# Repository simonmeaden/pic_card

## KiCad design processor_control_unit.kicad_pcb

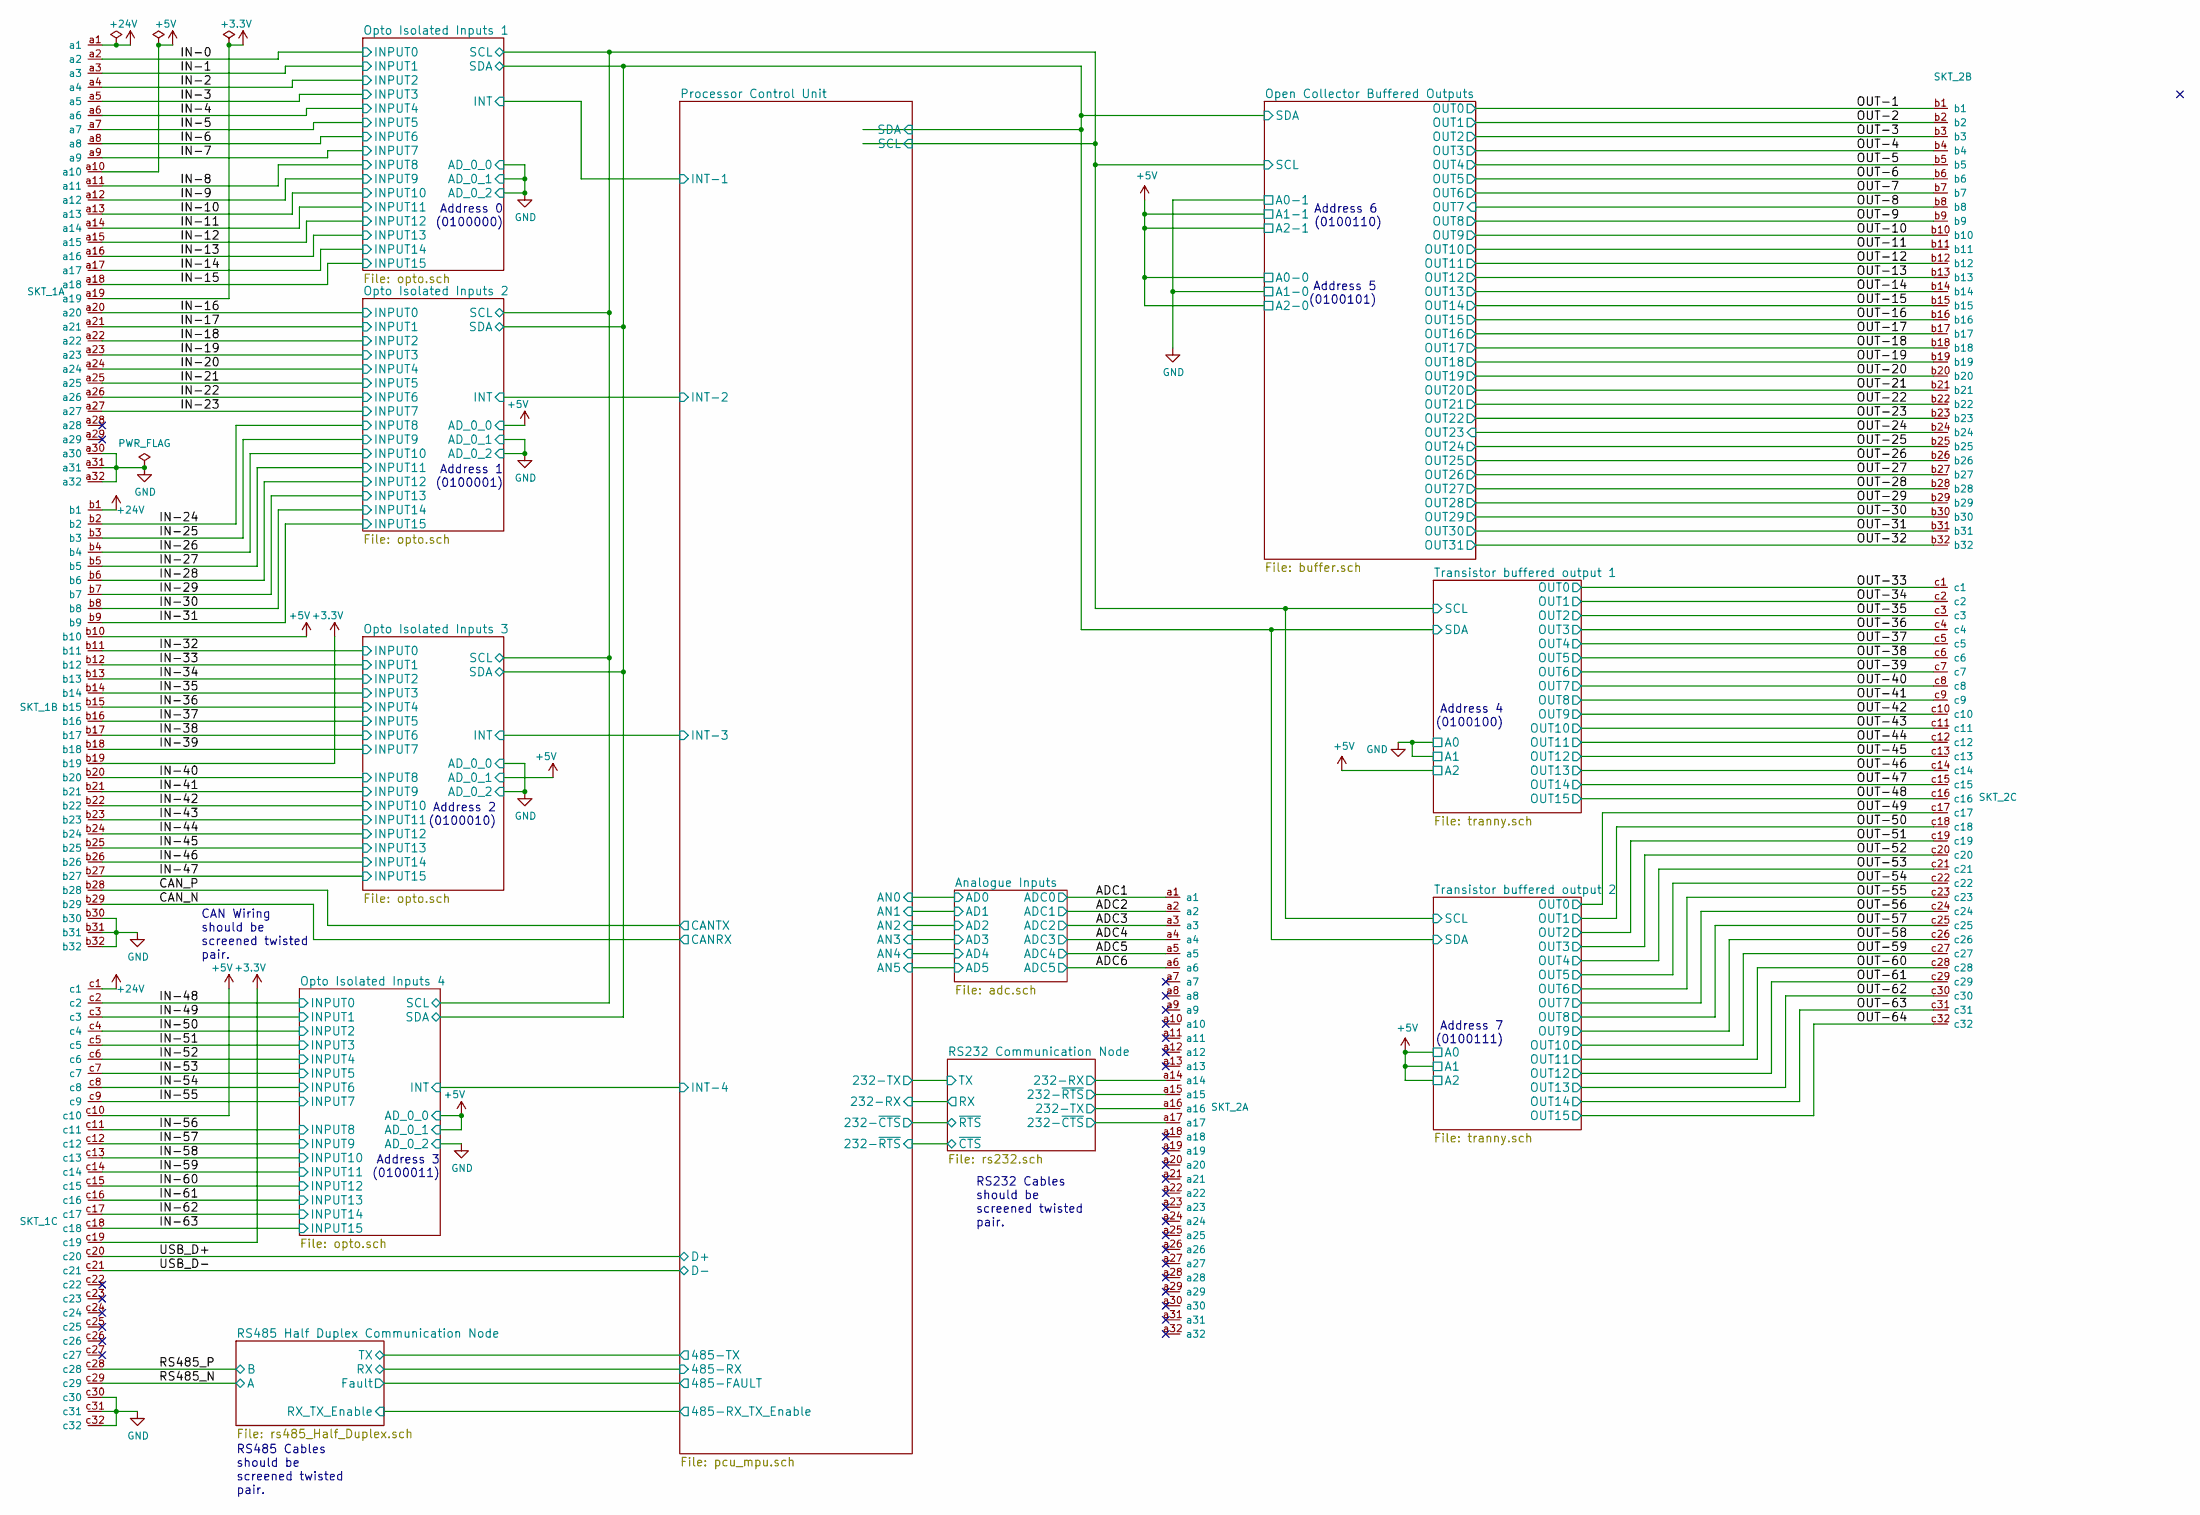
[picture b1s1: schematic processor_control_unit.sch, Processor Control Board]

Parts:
SKT_1, SKT_2: Conn_03x32_MountingPin_Pancon_RightAngled_Male; Pancon_100_3x32_P2.54mm_RightAngled_Male_PCB

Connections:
+3V3: SKT_1.a19, SKT_1.b19, SKT_1.c19
+5V: SKT_1.a10, SKT_1.b10, SKT_1.c10; also elsewhere on the board
+24V: SKT_1.a1, SKT_1.b1, SKT_1.c1; also elsewhere on the board
/ADC1: SKT_2.a1; also elsewhere on the board
/ADC2: SKT_2.a2; also elsewhere on the board
/ADC3: SKT_2.a3; also elsewhere on the board
/ADC4: SKT_2.a4; also elsewhere on the board
/ADC5: SKT_2.a5; also elsewhere on the board
/ADC6: SKT_2.a6; also elsewhere on the board
/CAN_N: SKT_1.b29; also elsewhere on the board
/CAN_P: SKT_1.b28; also elsewhere on the board
/IN-0: SKT_1.a2; also elsewhere on the board
/IN-1: SKT_1.a3; also elsewhere on the board
/IN-2: SKT_1.a4; also elsewhere on the board
/IN-3: SKT_1.a5; also elsewhere on the board
/IN-4: SKT_1.a6; also elsewhere on the board
/IN-5: SKT_1.a7; also elsewhere on the board
/IN-6: SKT_1.a8; also elsewhere on the board
/IN-7: SKT_1.a9; also elsewhere on the board
/IN-8: SKT_1.a11; also elsewhere on the board
/IN-9: SKT_1.a12; also elsewhere on the board
/IN-10: SKT_1.a13; also elsewhere on the board
/IN-11: SKT_1.a14; also elsewhere on the board
/IN-12: SKT_1.a15; also elsewhere on the board
/IN-13: SKT_1.a16; also elsewhere on the board
/IN-14: SKT_1.a17; also elsewhere on the board
/IN-15: SKT_1.a18; also elsewhere on the board
/IN-16: SKT_1.a20; also elsewhere on the board
/IN-17: SKT_1.a21; also elsewhere on the board
/IN-18: SKT_1.a22; also elsewhere on the board
/IN-19: SKT_1.a23; also elsewhere on the board
/IN-20: SKT_1.a24; also elsewhere on the board
/IN-21: SKT_1.a25; also elsewhere on the board
/IN-22: SKT_1.a26; also elsewhere on the board
/IN-23: SKT_1.a27; also elsewhere on the board
/IN-24: SKT_1.b2; also elsewhere on the board
/IN-25: SKT_1.b3; also elsewhere on the board
/IN-26: SKT_1.b4; also elsewhere on the board
/IN-27: SKT_1.b5; also elsewhere on the board
/IN-28: SKT_1.b6; also elsewhere on the board
/IN-29: SKT_1.b7; also elsewhere on the board
/IN-30: SKT_1.b8; also elsewhere on the board
/IN-31: SKT_1.b9; also elsewhere on the board
/IN-32: SKT_1.b11; also elsewhere on the board
/IN-33: SKT_1.b12; also elsewhere on the board
/IN-34: SKT_1.b13; also elsewhere on the board
/IN-35: SKT_1.b14; also elsewhere on the board
/IN-36: SKT_1.b15; also elsewhere on the board
/IN-37: SKT_1.b16; also elsewhere on the board
/IN-38: SKT_1.b17; also elsewhere on the board
/IN-39: SKT_1.b18; also elsewhere on the board
/IN-40: SKT_1.b20; also elsewhere on the board
/IN-41: SKT_1.b21; also elsewhere on the board
/IN-42: SKT_1.b22; also elsewhere on the board
/IN-43: SKT_1.b23; also elsewhere on the board
/IN-44: SKT_1.b24; also elsewhere on the board
/IN-45: SKT_1.b25; also elsewhere on the board
/IN-46: SKT_1.b26; also elsewhere on the board
/IN-47: SKT_1.b27; also elsewhere on the board
/IN-48: SKT_1.c2; also elsewhere on the board
/IN-49: SKT_1.c3; also elsewhere on the board
/IN-50: SKT_1.c4; also elsewhere on the board
/IN-51: SKT_1.c5; also elsewhere on the board
/IN-52: SKT_1.c6; also elsewhere on the board
/IN-53: SKT_1.c7; also elsewhere on the board
/IN-54: SKT_1.c8; also elsewhere on the board
/IN-55: SKT_1.c9; also elsewhere on the board
/IN-56: SKT_1.c11; also elsewhere on the board
/IN-57: SKT_1.c12; also elsewhere on the board
/IN-58: SKT_1.c13; also elsewhere on the board
/IN-59: SKT_1.c14; also elsewhere on the board
/IN-60: SKT_1.c15; also elsewhere on the board
/IN-61: SKT_1.c16; also elsewhere on the board
/IN-62: SKT_1.c17; also elsewhere on the board
/IN-63: SKT_1.c18; also elsewhere on the board
/OUT-1: SKT_2.b1; also elsewhere on the board
/OUT-2: SKT_2.b2; also elsewhere on the board
/OUT-3: SKT_2.b3; also elsewhere on the board
/OUT-4: SKT_2.b4; also elsewhere on the board
/OUT-5: SKT_2.b5; also elsewhere on the board
/OUT-6: SKT_2.b6; also elsewhere on the board
/OUT-7: SKT_2.b7; also elsewhere on the board
/OUT-8: SKT_2.b8; also elsewhere on the board
/OUT-9: SKT_2.b9; also elsewhere on the board
/OUT-10: SKT_2.b10; also elsewhere on the board
/OUT-11: SKT_2.b11; also elsewhere on the board
/OUT-12: SKT_2.b12; also elsewhere on the board
/OUT-13: SKT_2.b13; also elsewhere on the board
/OUT-14: SKT_2.b14; also elsewhere on the board
/OUT-15: SKT_2.b15; also elsewhere on the board
/OUT-16: SKT_2.b16; also elsewhere on the board
/OUT-17: SKT_2.b17; also elsewhere on the board
/OUT-18: SKT_2.b18; also elsewhere on the board
/OUT-19: SKT_2.b19; also elsewhere on the board
/OUT-20: SKT_2.b20; also elsewhere on the board
/OUT-21: SKT_2.b21; also elsewhere on the board
/OUT-22: SKT_2.b22; also elsewhere on the board
/OUT-23: SKT_2.b23; also elsewhere on the board
/OUT-24: SKT_2.b24; also elsewhere on the board
/OUT-25: SKT_2.b25; also elsewhere on the board
/OUT-26: SKT_2.b26; also elsewhere on the board
/OUT-27: SKT_2.b27; also elsewhere on the board
/OUT-28: SKT_2.b28; also elsewhere on the board
/OUT-29: SKT_2.b29; also elsewhere on the board
/OUT-30: SKT_2.b30; also elsewhere on the board
/OUT-31: SKT_2.b31; also elsewhere on the board
/OUT-32: SKT_2.b32; also elsewhere on the board
/OUT-33: SKT_2.c1; also elsewhere on the board
/OUT-34: SKT_2.c2; also elsewhere on the board
/OUT-35: SKT_2.c3; also elsewhere on the board
/OUT-36: SKT_2.c4; also elsewhere on the board
/OUT-37: SKT_2.c5; also elsewhere on the board
/OUT-38: SKT_2.c6; also elsewhere on the board
/OUT-39: SKT_2.c7; also elsewhere on the board
/OUT-40: SKT_2.c8; also elsewhere on the board
/OUT-41: SKT_2.c9; also elsewhere on the board
/OUT-42: SKT_2.c10; also elsewhere on the board
/OUT-43: SKT_2.c11; also elsewhere on the board
/OUT-44: SKT_2.c12; also elsewhere on the board
/OUT-45: SKT_2.c13; also elsewhere on the board
/OUT-46: SKT_2.c14; also elsewhere on the board
/OUT-47: SKT_2.c15; also elsewhere on the board
/OUT-48: SKT_2.c16; also elsewhere on the board
/OUT-49: SKT_2.c17; also elsewhere on the board
/OUT-50: SKT_2.c18; also elsewhere on the board
/OUT-51: SKT_2.c19; also elsewhere on the board
/OUT-52: SKT_2.c20; also elsewhere on the board
/OUT-53: SKT_2.c21; also elsewhere on the board
/OUT-54: SKT_2.c22; also elsewhere on the board
/OUT-55: SKT_2.c23; also elsewhere on the board
/OUT-56: SKT_2.c24; also elsewhere on the board
/OUT-57: SKT_2.c25; also elsewhere on the board
/OUT-58: SKT_2.c26; also elsewhere on the board
/OUT-59: SKT_2.c27; also elsewhere on the board
/OUT-60: SKT_2.c28; also elsewhere on the board
/OUT-61: SKT_2.c29; also elsewhere on the board
/OUT-62: SKT_2.c30; also elsewhere on the board
/OUT-63: SKT_2.c31; also elsewhere on the board
/OUT-64: SKT_2.c32; also elsewhere on the board
/RS232 Communication Node/232-RX: SKT_2.a14; also elsewhere on the board
/RS232 Communication Node/232-TX: SKT_2.a16; also elsewhere on the board
/RS232 Communication Node/232-~CTS~: SKT_2.a17; also elsewhere on the board
/RS232 Communication Node/232-~RTS~: SKT_2.a15; also elsewhere on the board
/RS485_N: SKT_1.c29; also elsewhere on the board
/RS485_P: SKT_1.c28; also elsewhere on the board
/USB_D+: SKT_1.c20; also elsewhere on the board
/USB_D-: SKT_1.c21; also elsewhere on the board
GND: SKT_1.a30, SKT_1.a31, SKT_1.a32, SKT_1.b30, SKT_1.b31, SKT_1.b32, SKT_1.c30, SKT_1.c31, SKT_1.c32; also elsewhere on the board

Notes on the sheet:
CAN Wiring should be screened twisted pair.
Address 0 (0100000)
Address 5 (0100101)
Address 4 (0100100)
Address 2 (0100010)
Address 3 (0100011)
Address 1 (0100001)
Address 6 (0100110)
Address 7 (0100111)
RS232 Cables should be screened twisted pair.
RS485 Cables should be screened twisted pair.

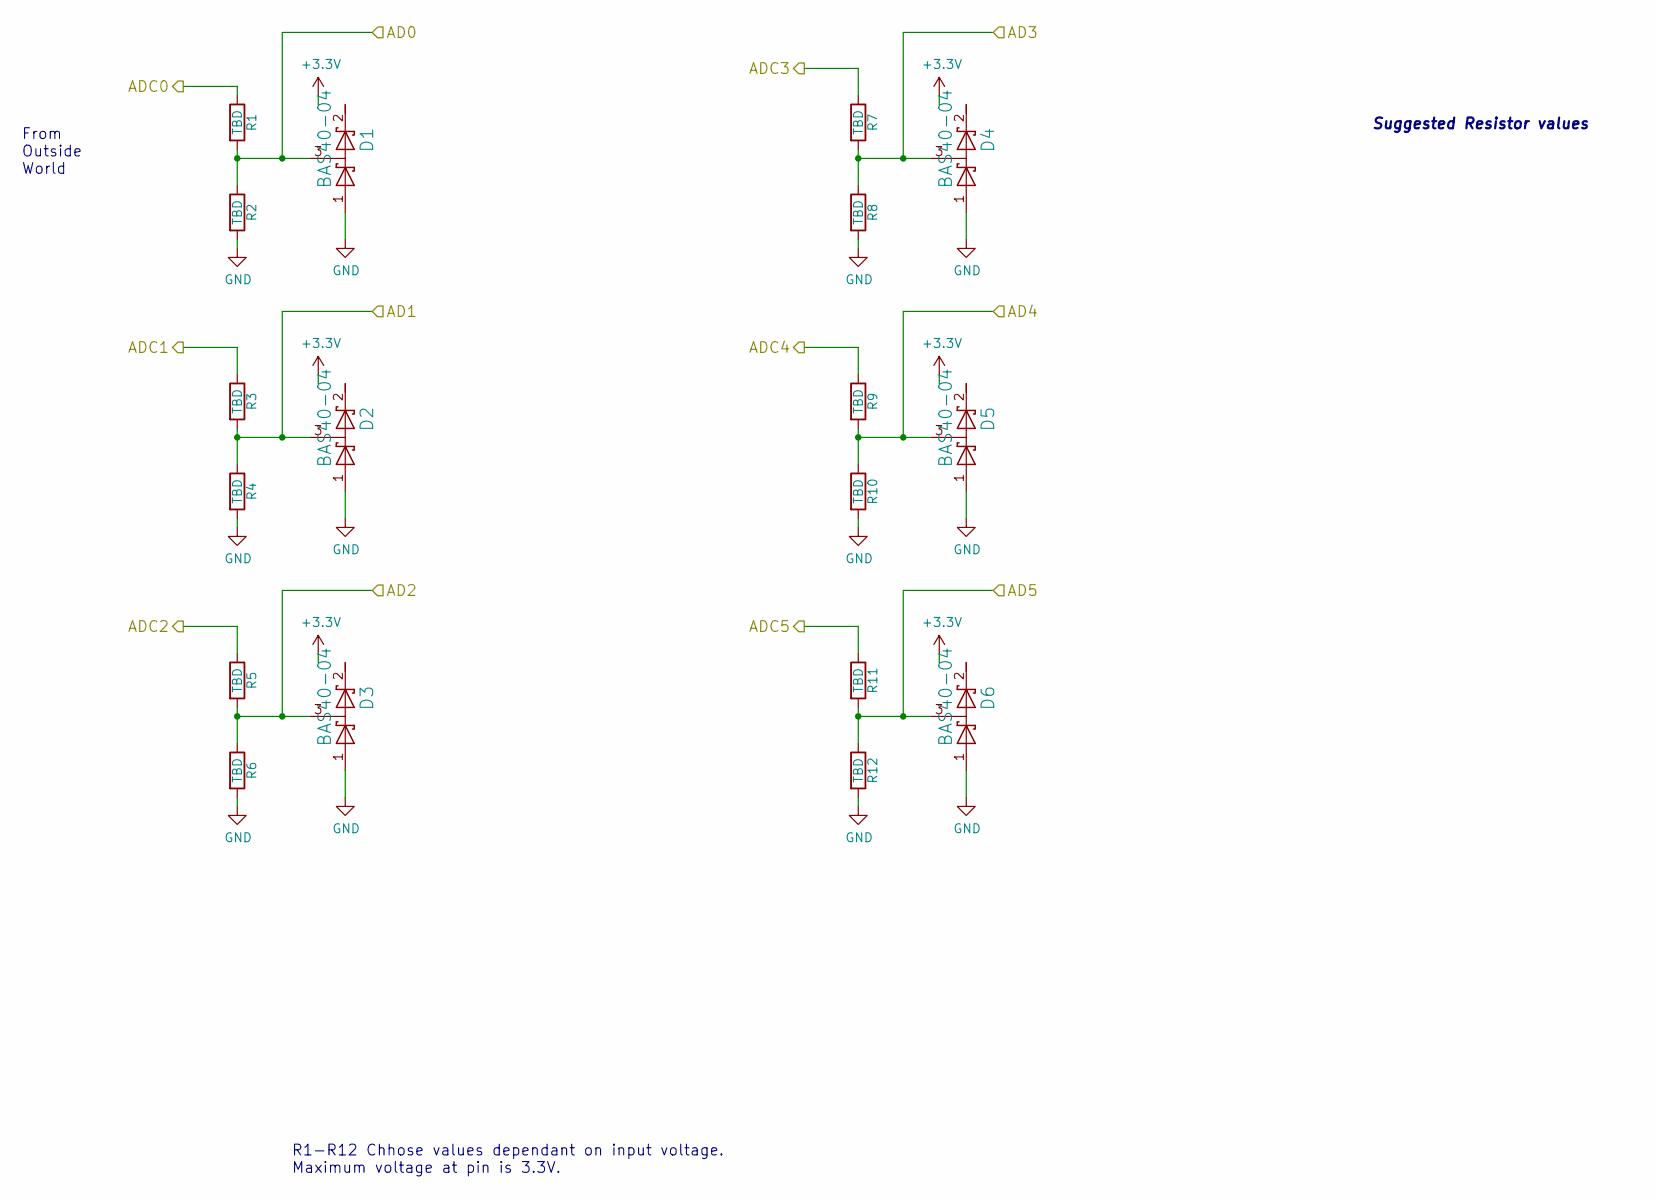
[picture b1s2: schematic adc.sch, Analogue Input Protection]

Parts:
D1, D2, D3, D4, D5, D6: BAS40-04; SOT23
R1, R2, R3, R4, R5, R6, R7, R8, R9, R10, R11, R12: TBD; R_0805_2012Metric

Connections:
/ADC1: R1.1; also elsewhere on the board
/ADC2: R3.1; also elsewhere on the board
/ADC3: R5.1; also elsewhere on the board
/ADC4: R7.1; also elsewhere on the board
/ADC5: R9.1; also elsewhere on the board
/ADC6: R11.1; also elsewhere on the board
/Analogue Inputs/AD0: D1.3 (common), R1.2, R2.1; also elsewhere on the board
/Analogue Inputs/AD1: D2.3 (common), R3.2, R4.1; also elsewhere on the board
/Analogue Inputs/AD2: D3.3 (common), R5.2, R6.1; also elsewhere on the board
/Analogue Inputs/AD3: D4.3 (common), R7.2, R8.1; also elsewhere on the board
/Analogue Inputs/AD4: D5.3 (common), R9.2, R10.1; also elsewhere on the board
/Analogue Inputs/AD5: D6.3 (common), R11.2, R12.1; also elsewhere on the board
GND: D1.1 (A), D2.1 (A), D3.1 (A), D4.1 (A), D5.1 (A), D6.1 (A), R2.2, R4.2, R6.2, R8.2, R10.2, R12.2; also elsewhere on the board

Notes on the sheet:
From Outside World
R1-R12 Chhose values dependant on input voltage. Maximum voltage at pin is 3.3V.
Suggested Resistor values

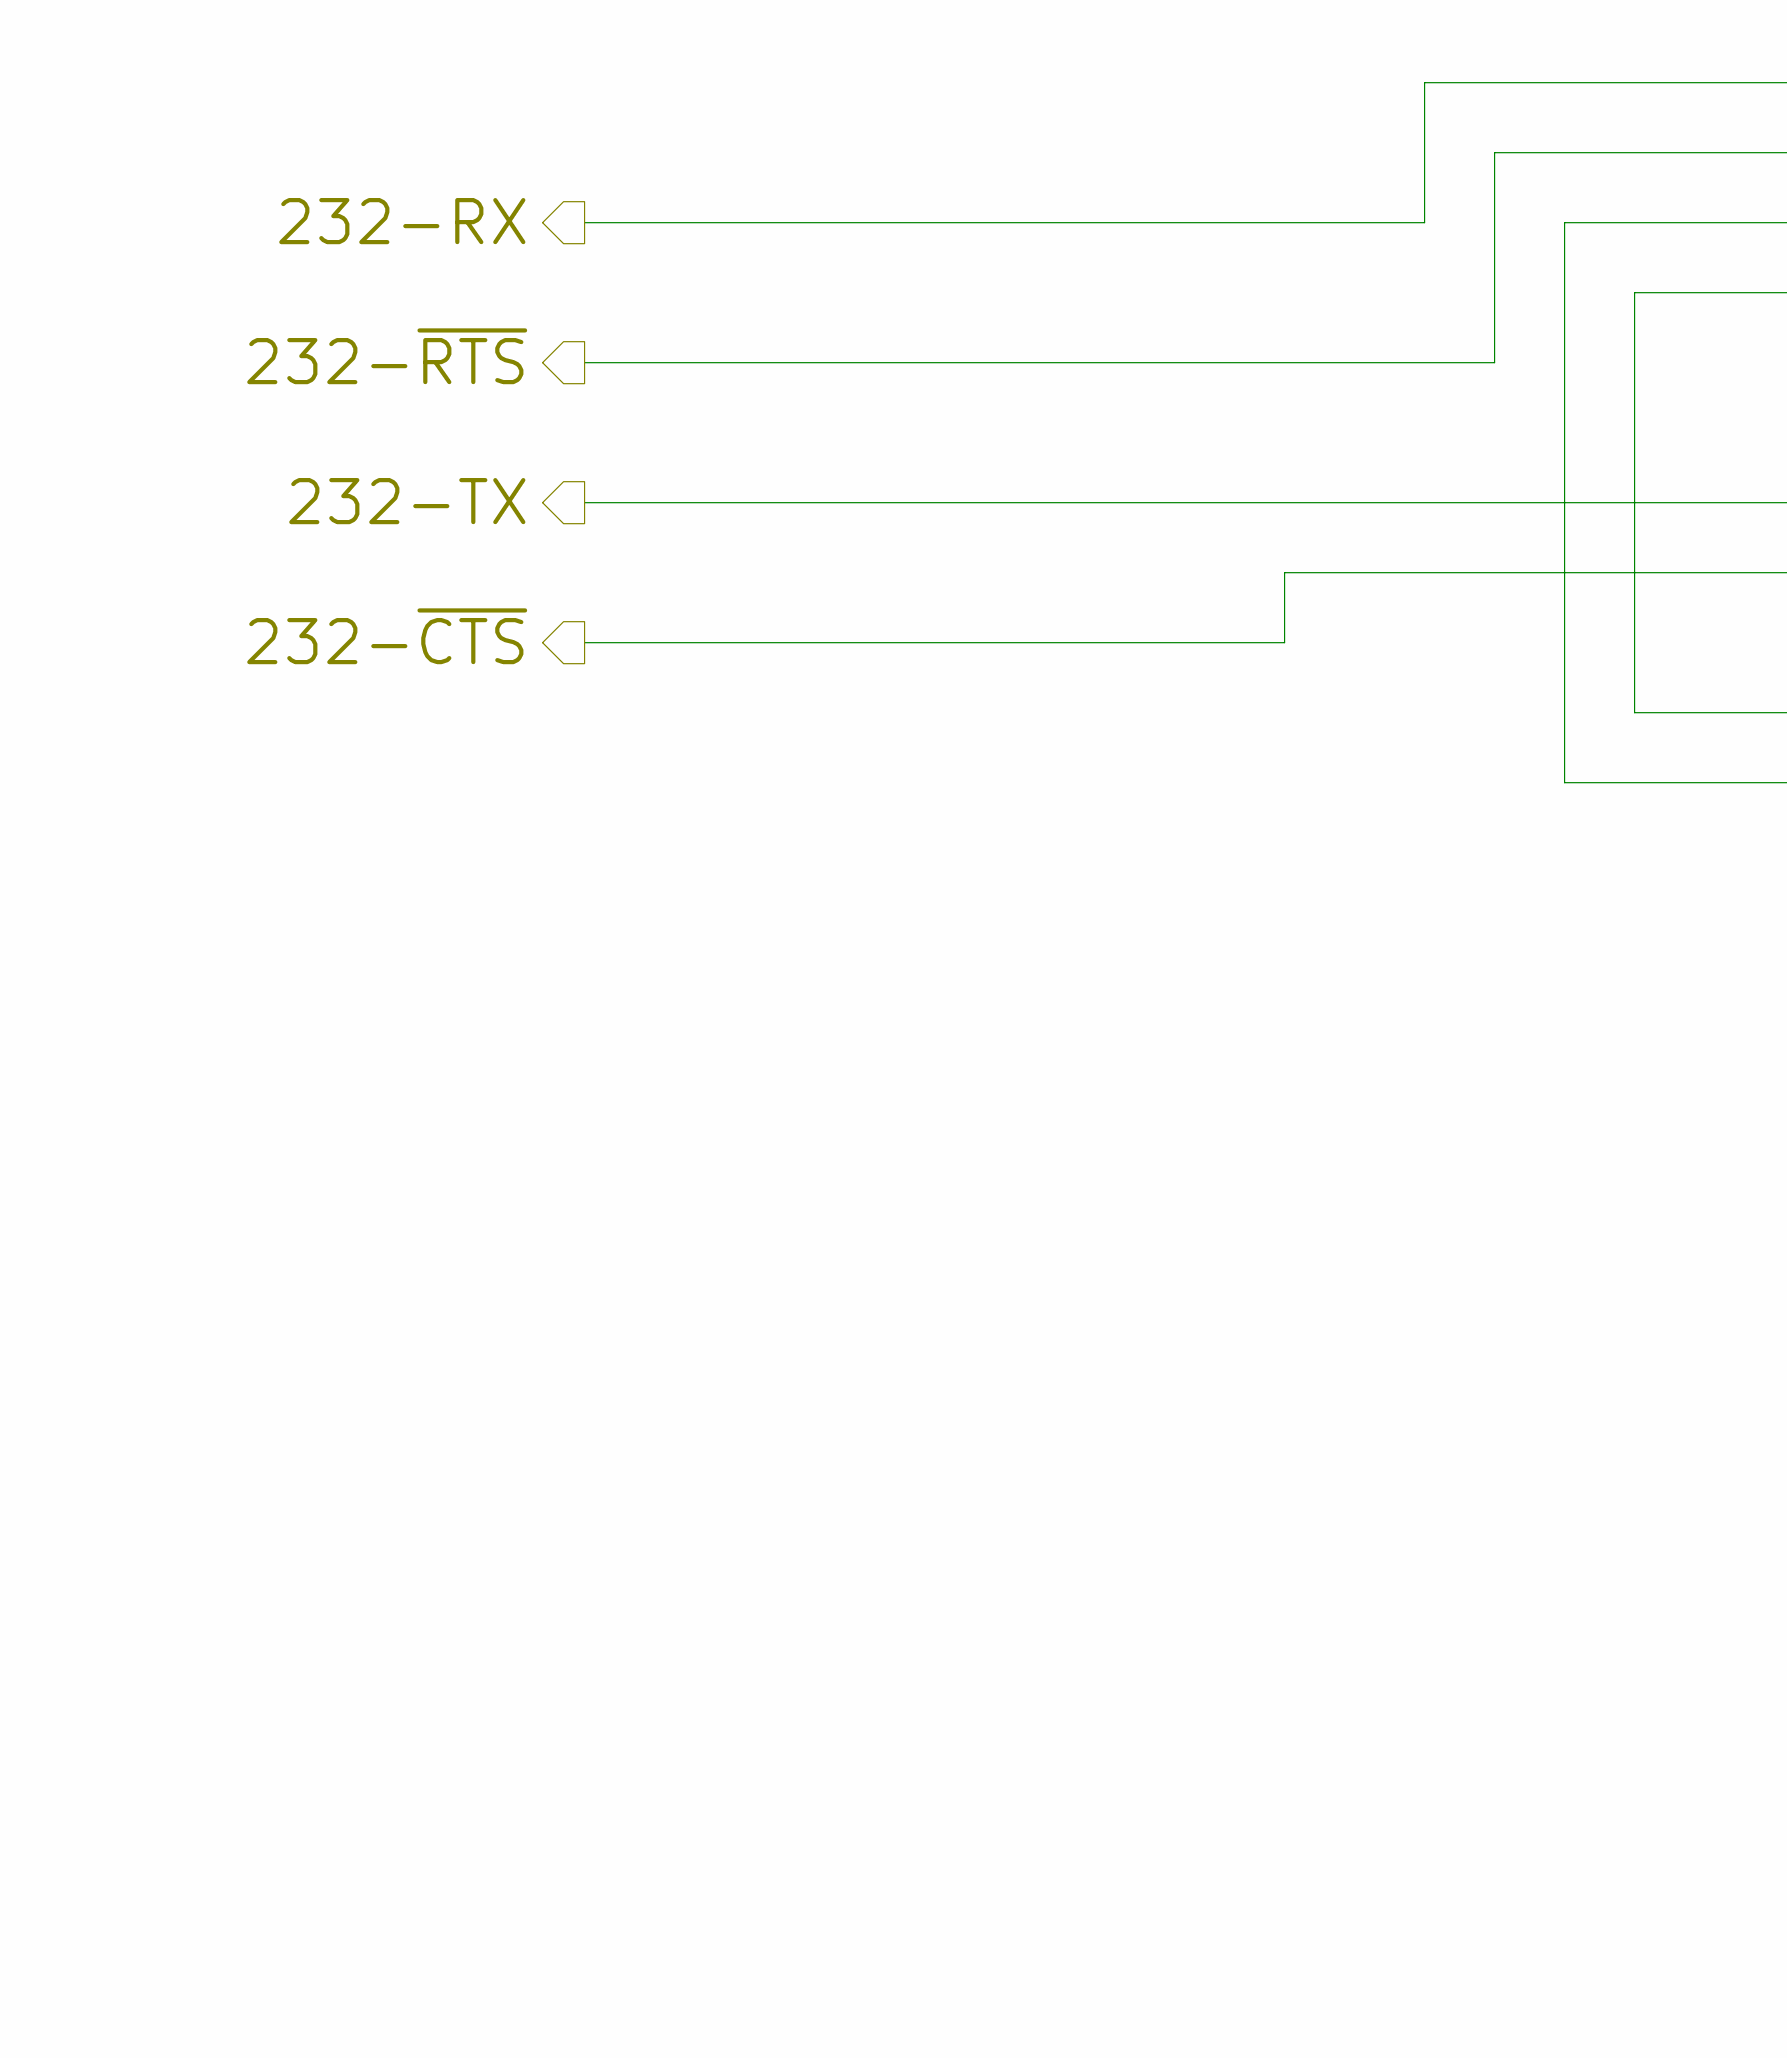
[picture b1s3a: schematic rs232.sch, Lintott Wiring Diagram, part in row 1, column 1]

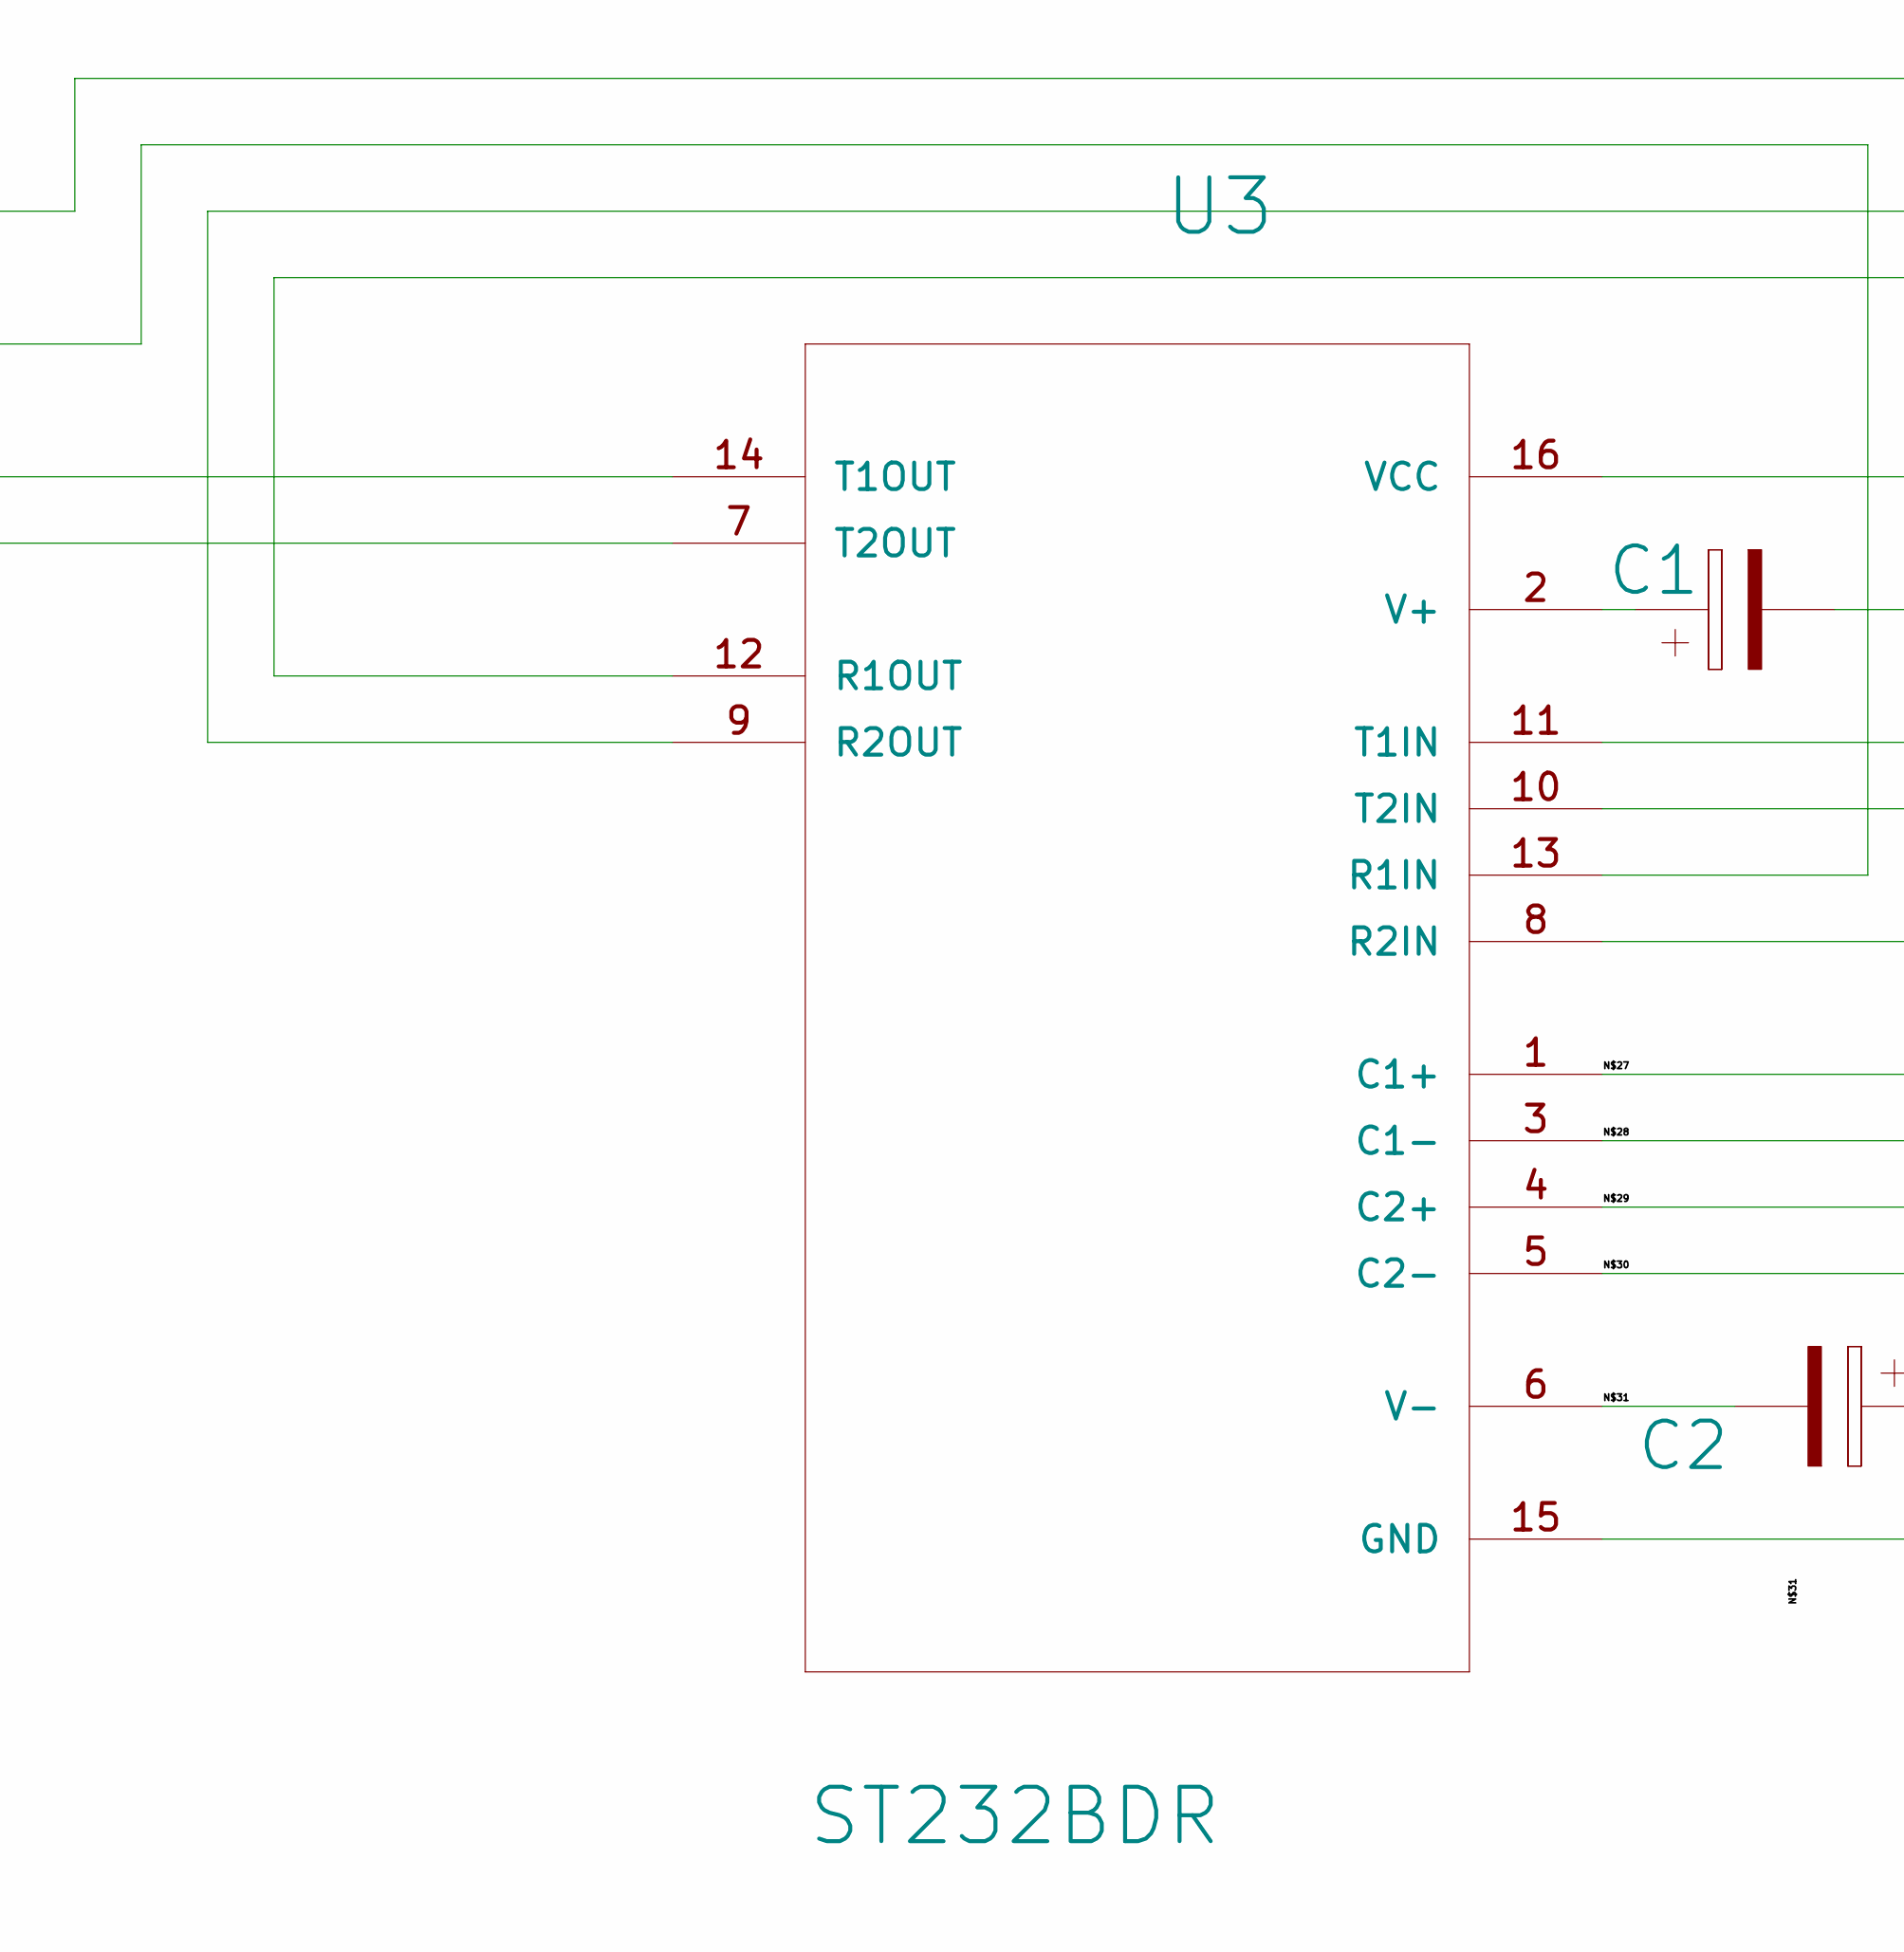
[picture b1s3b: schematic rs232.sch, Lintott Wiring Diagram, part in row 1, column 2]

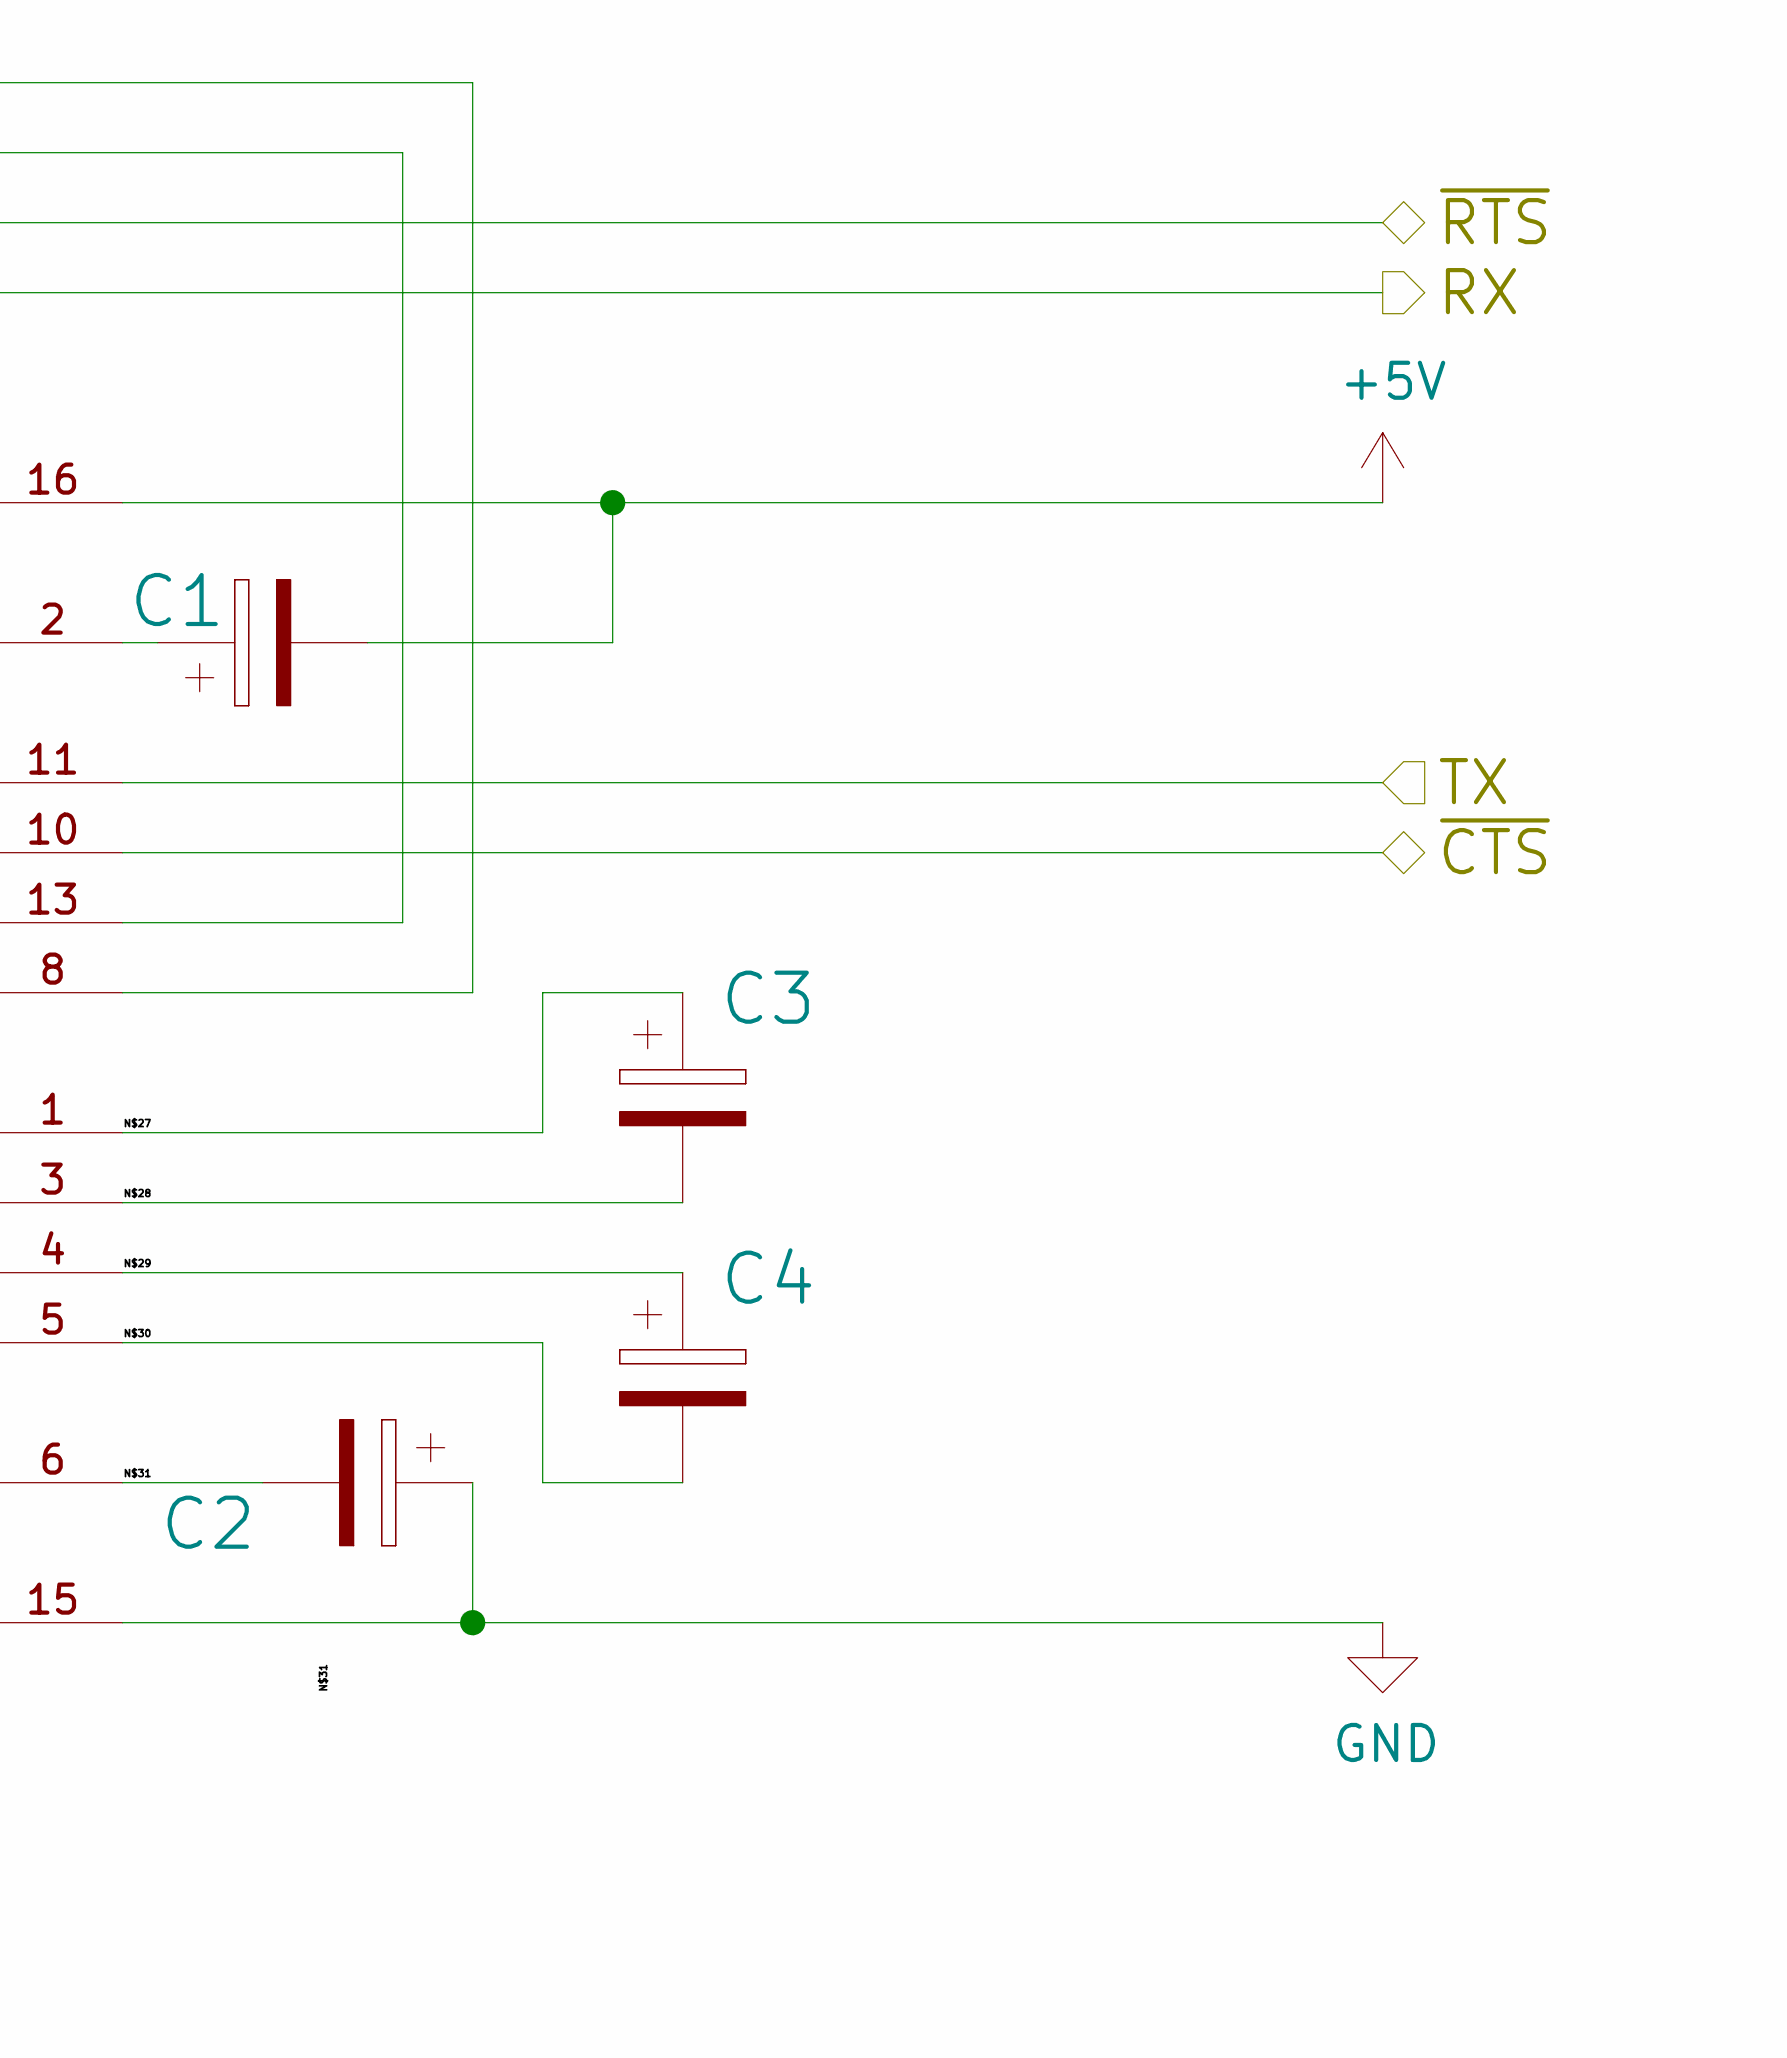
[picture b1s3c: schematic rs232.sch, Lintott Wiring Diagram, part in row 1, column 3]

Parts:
C1, C2, C3, C4: 1uF; Kemet_A_3216-18W
U3: ST232BDR; SOIC127P600X175-16N

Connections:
+5V: C1.2, U3.16 (VCC); also elsewhere on the board
/Processor Control Unit/232-RX: U3.12 (R1OUT); also elsewhere on the board
/Processor Control Unit/232-TX: U3.11 (T1IN); also elsewhere on the board
/Processor Control Unit/232-~CTS~: U3.9 (R2OUT); also elsewhere on the board
/Processor Control Unit/232-~RTS~: U3.10 (T2IN); also elsewhere on the board
/RS232 Communication Node/232-RX: U3.8 (R2IN); also elsewhere on the board
/RS232 Communication Node/232-TX: U3.14 (T1OUT); also elsewhere on the board
/RS232 Communication Node/232-~CTS~: U3.7 (T2OUT); also elsewhere on the board
/RS232 Communication Node/232-~RTS~: U3.13 (R1IN); also elsewhere on the board
/RS232 Communication Node/N$27: C3.1, U3.1 (C1+)
/RS232 Communication Node/N$28: C3.2, U3.3 (C1-)
/RS232 Communication Node/N$29: C4.1, U3.4 (C2+)
/RS232 Communication Node/N$30: C4.2, U3.5 (C2-)
/RS232 Communication Node/N$31: C2.2, U3.6 (V-)
GND: C2.1, U3.15 (GND); also elsewhere on the board
unnamed: C1.1, U3.2 (V+)

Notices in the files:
adc.sch:
Copyright © Simon Meaden
